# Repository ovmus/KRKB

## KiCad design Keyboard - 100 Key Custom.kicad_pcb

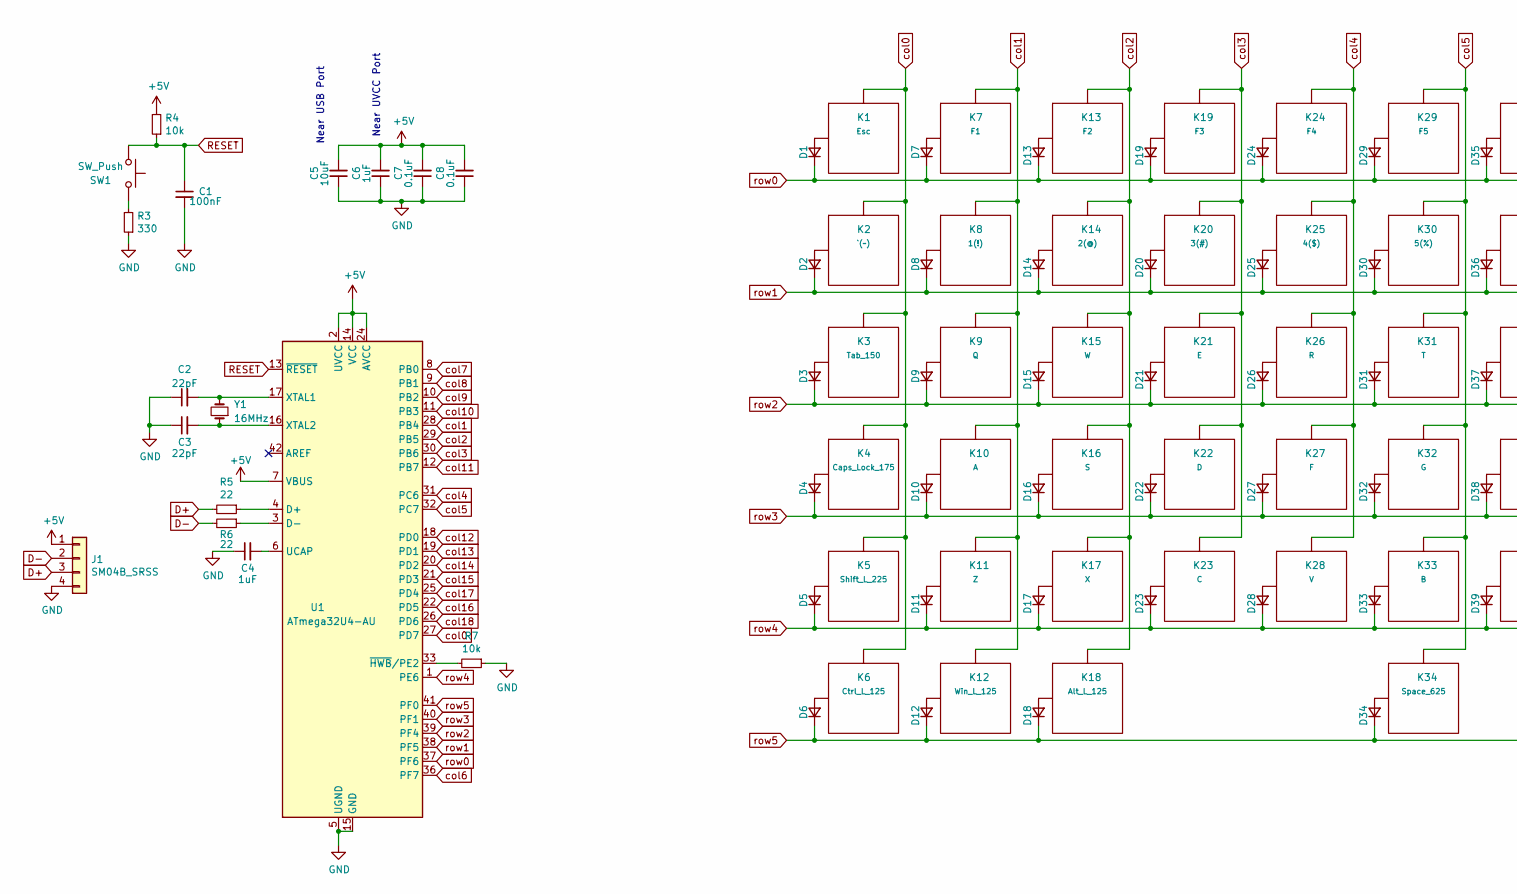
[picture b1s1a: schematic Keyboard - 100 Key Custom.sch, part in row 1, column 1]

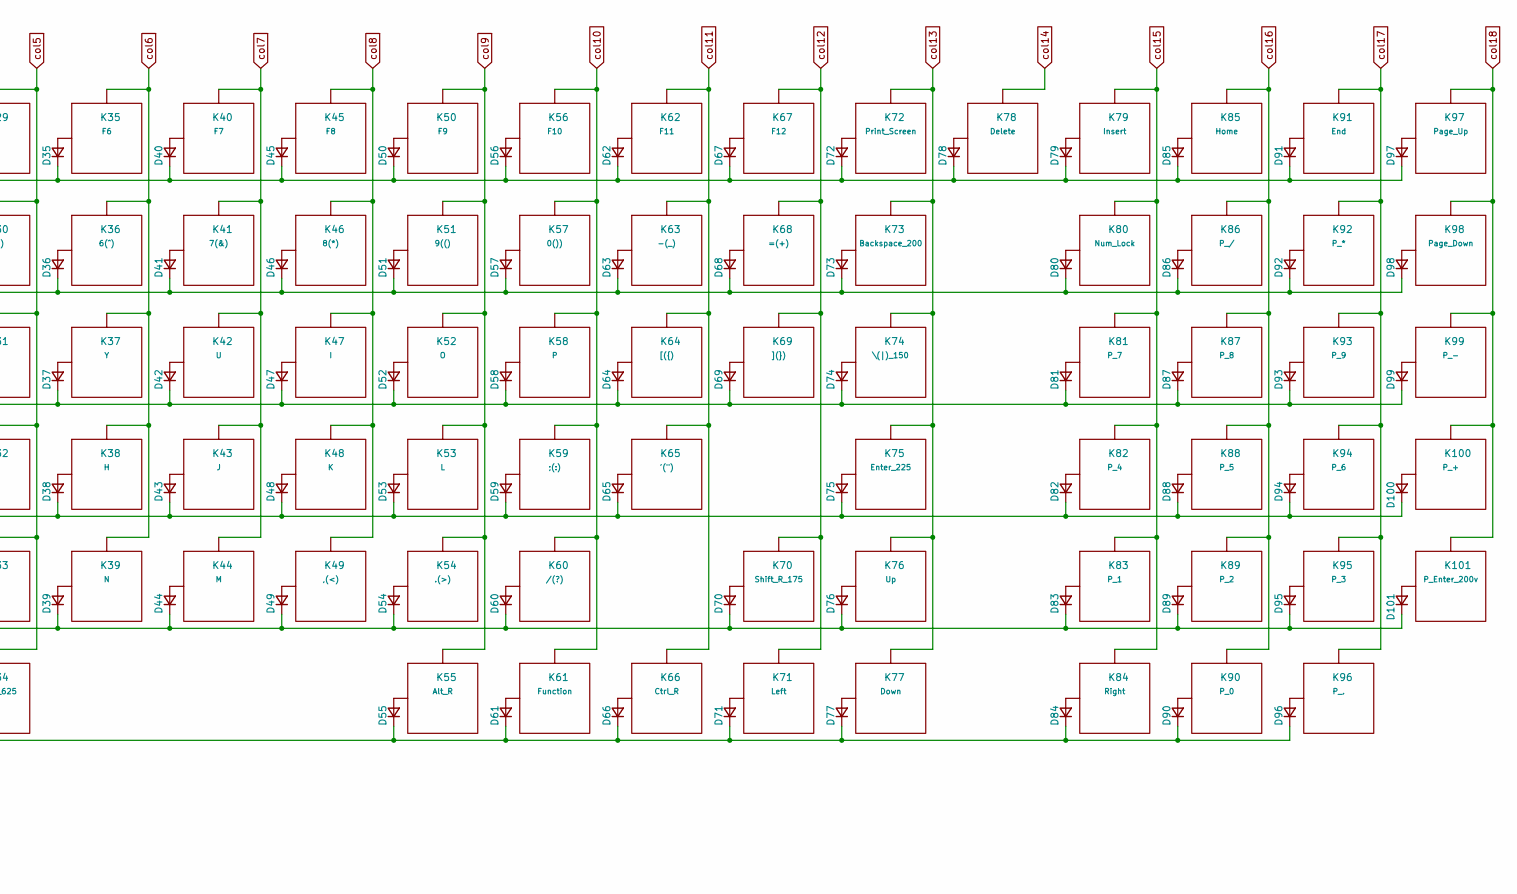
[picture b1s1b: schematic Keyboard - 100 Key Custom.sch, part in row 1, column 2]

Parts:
C1: 100nF; C_0805_2012Metric_Pad1.15x1.40mm_HandSolder
C2, C3: 22pF; C_0805_2012Metric_Pad1.15x1.40mm_HandSolder
C4, C6: 1uF; C_0805_2012Metric_Pad1.15x1.40mm_HandSolder
C5: 10uF; C_0805_2012Metric_Pad1.15x1.40mm_HandSolder
C7, C8: 0.1uF; C_0805_2012Metric_Pad1.15x1.40mm_HandSolder
D1, D2, D3, D4, D5, D6, D7, D8, D9, D10, D11, D12, D13, D14, D15, D16, D17, D18, D19, D20, D21, D22, D23, D24, D25, D26, D27, D28, D29, D30, D31, D32, D33, D34, D35, D36, D37, D38, D39, D40, D41, D42, D43, D44, D45, D46, D47, D48, D49, D50, D51, D52, D53, D54, D55, D56, D57, D58, D59, D60, D61, D62, D63, D64, D65, D66, D67, D68, D69, D70, D71, D72, D73, D74, D75, D76, D77, D78, D79, D80, D81, D82, D83, D84, D85, D86, D87, D88, D89, D90, D91, D92, D93, D94, D95, D96, D97, D98, D99, D100, D101: D_Small; D_SOD-123
J1: SM04B_SRSS; SM04B-SRSS
K1: Esc; MX100
K2: `(~~); MX100
K3: Tab_150; MX150
K4: Caps_Lock_175; MX175
K5: Shift_L_225; MX225
K6: Ctrl_L_125; MX125
K7: F1; MX100
K8: 1(!); MX100
K9: Q; MX100
K10: A; MX100
K11: Z; MX100
K12: Win_L_125; MX125
K13: F2; MX100
K14: 2(@); MX100
K15: W; MX100
K16: S; MX100
K17: X; MX100
K18: Alt_L_125; MX125
K19: F3; MX100
K20: 3(#); MX100
K21: E; MX100
K22: D; MX100
K23: C; MX100
K24: F4; MX100
K25: 4($); MX100
K26: R; MX100
K27: F; MX100
K28: V; MX100
K29: F5; MX100
K30: 5(%); MX100
K31: T; MX100
K32: G; MX100
K33: B; MX100
K34: Space_625; MX625R
K35: F6; MX100
K36: 6(^); MX100
K37: Y; MX100
K38: H; MX100
K39: N; MX100
K40: F7; MX100
K41: 7(&); MX100
K42: U; MX100
K43: J; MX100
K44: M; MX100
K45: F8; MX100
K46: 8(*); MX100
K47: I; MX100
K48: K; MX100
K49: ,(<); MX100
K50: F9; MX100
K51: 9((); MX100
K52: O; MX100
K53: L; MX100
K54: .(>); MX100
K55: Alt_R; MX100
K56: F10; MX100
K57: 0()); MX100
K58: P; MX100
K59: ;(:); MX100
K60: /(?); MX100
K61: Function; MX100
K62: F11; MX100
K63: -(_); MX100
K64: [({); MX100
K65: '(\"); MX100
K66: Ctrl_R; MX100
K67: F12; MX100
K68: =(+); MX100
K69: ](}); MX100
K70: Shift_R_175; MX175
K71: Left; MX100
K72: Print_Screen; MX100
K73: Backspace_200; MX200
K74: \\(|)_150; MX150
K75: Enter_225; MX225
K76: Up; MX100
K77: Down; MX100
K78: Delete; MX100
K79: Insert; MX100
K80: Num_Lock; MX100
K81: P_7; MX100
K82: P_4; MX100
K83: P_1; MX100
K84: Right; MX100
K85: Home; MX100
K86: P_/; MX100
K87: P_8; MX100
K88: P_5; MX100
K89: P_2; MX100
K90: P_0; MX100
K91: End; MX100
K92: P_*; MX100
K93: P_9; MX100
K94: P_6; MX100
K95: P_3; MX100
K96: P_.; MX100
K97: Page_Up; MX100
K98: Page_Down; MX100
K99: P_-; MX100
K100: P_+; MX100
K101: P_Enter_200v; MX200V
R3: 330; C_1206_3216Metric_Pad1.42x1.75mm_HandSolder
R4, R7: 10k; C_1206_3216Metric_Pad1.42x1.75mm_HandSolder
R5, R6: 22; C_1206_3216Metric_Pad1.42x1.75mm_HandSolder
SW1: SW_Push; K2-1187SQ-A4SW-06
U1: ATmega32U4-AU; TQPF-44_10x10mm_P0.8mm
Y1: 16MHz; Crystal_SMD_5032-2Pin_5.0x3.2mm_HandSoldering

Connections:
+5V: C5.2, C6.2, C7.2, C8.2, J1.1, R4.2, U1.2 (UVCC), U1.7 (VBUS), U1.14 (VCC), U1.24 (AVCC), U1.34 (VCC), U1.44 (AVCC)
D+: J1.3, R5.2
D-: J1.2, R6.2
GND: C1.2, C2.1, C3.1, C4.1, C5.1, C6.1, C7.1, C8.1, J1.4, R3.1, R7.1, U1.5 (UGND), U1.15 (GND), U1.23 (GND), U1.35 (GND), U1.43 (GND)
unnamed: C2.2, U1.17 (XTAL1), Y1.2
unnamed: C3.2, U1.16 (XTAL2), Y1.1
unnamed: C4.2, U1.6 (UCAP)
unnamed: D1.2 (A), K1.1 (Col)
unnamed: D2.2 (A), K2.1 (Col)
unnamed: D3.2 (A), K3.1 (Col)
unnamed: D4.2 (A), K4.1 (Col)
unnamed: D5.2 (A), K5.1 (Col)
unnamed: D6.2 (A), K6.1 (Col)
unnamed: D7.2 (A), K7.1 (Col)
unnamed: D8.2 (A), K8.1 (Col)
unnamed: D9.2 (A), K9.1 (Col)
unnamed: D10.2 (A), K10.1 (Col)
unnamed: D11.2 (A), K11.1 (Col)
unnamed: D12.2 (A), K12.1 (Col)
unnamed: D13.2 (A), K13.1 (Col)
unnamed: D14.2 (A), K14.1 (Col)
unnamed: D15.2 (A), K15.1 (Col)
unnamed: D16.2 (A), K16.1 (Col)
unnamed: D17.2 (A), K17.1 (Col)
unnamed: D18.2 (A), K18.1 (Col)
unnamed: D19.2 (A), K19.1 (Col)
unnamed: D20.2 (A), K20.1 (Col)
unnamed: D21.2 (A), K21.1 (Col)
unnamed: D22.2 (A), K22.1 (Col)
unnamed: D23.2 (A), K23.1 (Col)
unnamed: D24.2 (A), K24.1 (Col)
unnamed: D25.2 (A), K25.1 (Col)
unnamed: D26.2 (A), K26.1 (Col)
unnamed: D27.2 (A), K27.1 (Col)
unnamed: D28.2 (A), K28.1 (Col)
unnamed: D29.2 (A), K29.1 (Col)
unnamed: D30.2 (A), K30.1 (Col)
unnamed: D31.2 (A), K31.1 (Col)
unnamed: D32.2 (A), K32.1 (Col)
unnamed: D33.2 (A), K33.1 (Col)
unnamed: D34.2 (A), K34.1 (Col)
unnamed: D35.2 (A), K35.1 (Col)
unnamed: D36.2 (A), K36.1 (Col)
unnamed: D37.2 (A), K37.1 (Col)
unnamed: D38.2 (A), K38.1 (Col)
unnamed: D39.2 (A), K39.1 (Col)
unnamed: D40.2 (A), K40.1 (Col)
unnamed: D41.2 (A), K41.1 (Col)
unnamed: D42.2 (A), K42.1 (Col)
unnamed: D43.2 (A), K43.1 (Col)
unnamed: D44.2 (A), K44.1 (Col)
unnamed: D45.2 (A), K45.1 (Col)
unnamed: D46.2 (A), K46.1 (Col)
unnamed: D47.2 (A), K47.1 (Col)
unnamed: D48.2 (A), K48.1 (Col)
unnamed: D49.2 (A), K49.1 (Col)
unnamed: D50.2 (A), K50.1 (Col)
unnamed: D51.2 (A), K51.1 (Col)
unnamed: D52.2 (A), K52.1 (Col)
unnamed: D53.2 (A), K53.1 (Col)
unnamed: D54.2 (A), K54.1 (Col)
unnamed: D55.2 (A), K55.1 (Col)
unnamed: D56.2 (A), K56.1 (Col)
unnamed: D57.2 (A), K57.1 (Col)
unnamed: D58.2 (A), K58.1 (Col)
unnamed: D59.2 (A), K59.1 (Col)
unnamed: D60.2 (A), K60.1 (Col)
unnamed: D61.2 (A), K61.1 (Col)
unnamed: D62.2 (A), K62.1 (Col)
unnamed: D63.2 (A), K63.1 (Col)
unnamed: D64.2 (A), K64.1 (Col)
unnamed: D65.2 (A), K65.1 (Col)
unnamed: D66.2 (A), K66.1 (Col)
unnamed: D67.2 (A), K67.1 (Col)
unnamed: D68.2 (A), K68.1 (Col)
unnamed: D69.2 (A), K69.1 (Col)
unnamed: D70.2 (A), K70.1 (Col)
unnamed: D71.2 (A), K71.1 (Col)
unnamed: D72.2 (A), K72.1 (Col)
unnamed: D73.2 (A), K73.1 (Col)
unnamed: D74.2 (A), K74.1 (Col)
unnamed: D75.2 (A), K75.1 (Col)
unnamed: D76.2 (A), K76.1 (Col)
unnamed: D77.2 (A), K77.1 (Col)
unnamed: D78.2 (A), K78.1 (Col)
unnamed: D79.2 (A), K79.1 (Col)
unnamed: D80.2 (A), K80.1 (Col)
unnamed: D81.2 (A), K81.1 (Col)
unnamed: D82.2 (A), K82.1 (Col)
unnamed: D83.2 (A), K83.1 (Col)
unnamed: D84.2 (A), K84.1 (Col)
unnamed: D85.2 (A), K85.1 (Col)
unnamed: D86.2 (A), K86.1 (Col)
unnamed: D87.2 (A), K87.1 (Col)
unnamed: D88.2 (A), K88.1 (Col)
unnamed: D89.2 (A), K89.1 (Col)
unnamed: D90.2 (A), K90.1 (Col)
unnamed: D91.2 (A), K91.1 (Col)
unnamed: D92.2 (A), K92.1 (Col)
unnamed: D93.2 (A), K93.1 (Col)
unnamed: D94.2 (A), K94.1 (Col)
unnamed: D95.2 (A), K95.1 (Col)
unnamed: D96.2 (A), K96.1 (Col)
unnamed: D97.2 (A), K97.1 (Col)
unnamed: D98.2 (A), K98.1 (Col)
unnamed: D99.2 (A), K99.1 (Col)
unnamed: D100.2 (A), K100.1 (Col)
unnamed: D101.2 (A), K101.1 (Col)
unnamed: R3.2, SW1.2
unnamed: R5.1, U1.4 (D+)
unnamed: R6.1, U1.3 (D-)
unnamed: R7.2, U1.33 (~HWB~/PE2)
RESET: C1.1, R4.1, SW1.1, U1.13 (~RESET)
col0: K1.2 (Row), K2.2 (Row), K3.2 (Row), K4.2 (Row), K5.2 (Row), K6.2 (Row), U1.27 (PD7)
col1: K7.2 (Row), K8.2 (Row), K9.2 (Row), K10.2 (Row), K11.2 (Row), K12.2 (Row), U1.28 (PB4)
col2: K13.2 (Row), K14.2 (Row), K15.2 (Row), K16.2 (Row), K17.2 (Row), K18.2 (Row), U1.29 (PB5)
col3: K19.2 (Row), K20.2 (Row), K21.2 (Row), K22.2 (Row), K23.2 (Row), U1.30 (PB6)
col4: K24.2 (Row), K25.2 (Row), K26.2 (Row), K27.2 (Row), K28.2 (Row), U1.31 (PC6)
col5: K29.2 (Row), K30.2 (Row), K31.2 (Row), K32.2 (Row), K33.2 (Row), K34.2 (Row), U1.32 (PC7)
col6: K35.2 (Row), K36.2 (Row), K37.2 (Row), K38.2 (Row), K39.2 (Row), U1.36 (PF7)
col7: K40.2 (Row), K41.2 (Row), K42.2 (Row), K43.2 (Row), K44.2 (Row), U1.8 (PB0)
col8: K45.2 (Row), K46.2 (Row), K47.2 (Row), K48.2 (Row), K49.2 (Row), U1.9 (PB1)
col9: K50.2 (Row), K51.2 (Row), K52.2 (Row), K53.2 (Row), K54.2 (Row), K55.2 (Row), U1.10 (PB2)
col10: K56.2 (Row), K57.2 (Row), K58.2 (Row), K59.2 (Row), K60.2 (Row), K61.2 (Row), U1.11 (PB3)
col11: K62.2 (Row), K63.2 (Row), K64.2 (Row), K65.2 (Row), K66.2 (Row), U1.12 (PB7)
col12: K67.2 (Row), K68.2 (Row), K69.2 (Row), K70.2 (Row), K71.2 (Row), U1.18 (PD0)
col13: K72.2 (Row), K73.2 (Row), K74.2 (Row), K75.2 (Row), K76.2 (Row), K77.2 (Row), U1.19 (PD1)
col14: K78.2 (Row), U1.20 (PD2)
col15: K79.2 (Row), K80.2 (Row), K81.2 (Row), K82.2 (Row), K83.2 (Row), K84.2 (Row), U1.21 (PD3)
col16: K85.2 (Row), K86.2 (Row), K87.2 (Row), K88.2 (Row), K89.2 (Row), K90.2 (Row), U1.22 (PD5)
col17: K91.2 (Row), K92.2 (Row), K93.2 (Row), K94.2 (Row), K95.2 (Row), K96.2 (Row), U1.25 (PD4)
col18: K97.2 (Row), K98.2 (Row), K99.2 (Row), K100.2 (Row), K101.2 (Row), U1.26 (PD6)
row0: D1.1 (K), D7.1 (K), D13.1 (K), D19.1 (K), D24.1 (K), D29.1 (K), D35.1 (K), D40.1 (K), D45.1 (K), D50.1 (K), D56.1 (K), D62.1 (K), D67.1 (K), D72.1 (K), D78.1 (K), D79.1 (K), D85.1 (K), D91.1 (K), D97.1 (K), U1.37 (PF6)
row1: D2.1 (K), D8.1 (K), D14.1 (K), D20.1 (K), D25.1 (K), D30.1 (K), D36.1 (K), D41.1 (K), D46.1 (K), D51.1 (K), D57.1 (K), D63.1 (K), D68.1 (K), D73.1 (K), D80.1 (K), D86.1 (K), D92.1 (K), D98.1 (K), U1.38 (PF5)
row2: D3.1 (K), D9.1 (K), D15.1 (K), D21.1 (K), D26.1 (K), D31.1 (K), D37.1 (K), D42.1 (K), D47.1 (K), D52.1 (K), D58.1 (K), D64.1 (K), D69.1 (K), D74.1 (K), D81.1 (K), D87.1 (K), D93.1 (K), D99.1 (K), U1.39 (PF4)
row3: D4.1 (K), D10.1 (K), D16.1 (K), D22.1 (K), D27.1 (K), D32.1 (K), D38.1 (K), D43.1 (K), D48.1 (K), D53.1 (K), D59.1 (K), D65.1 (K), D75.1 (K), D82.1 (K), D88.1 (K), D94.1 (K), D100.1 (K), U1.40 (PF1)
row4: D5.1 (K), D11.1 (K), D17.1 (K), D23.1 (K), D28.1 (K), D33.1 (K), D39.1 (K), D44.1 (K), D49.1 (K), D54.1 (K), D60.1 (K), D70.1 (K), D76.1 (K), D83.1 (K), D89.1 (K), D95.1 (K), D101.1 (K), U1.1 (PE6)
row5: D6.1 (K), D12.1 (K), D18.1 (K), D34.1 (K), D55.1 (K), D61.1 (K), D66.1 (K), D71.1 (K), D77.1 (K), D84.1 (K), D90.1 (K), D96.1 (K), U1.41 (PF0)

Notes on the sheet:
Near USB Port
Near UVCC Port

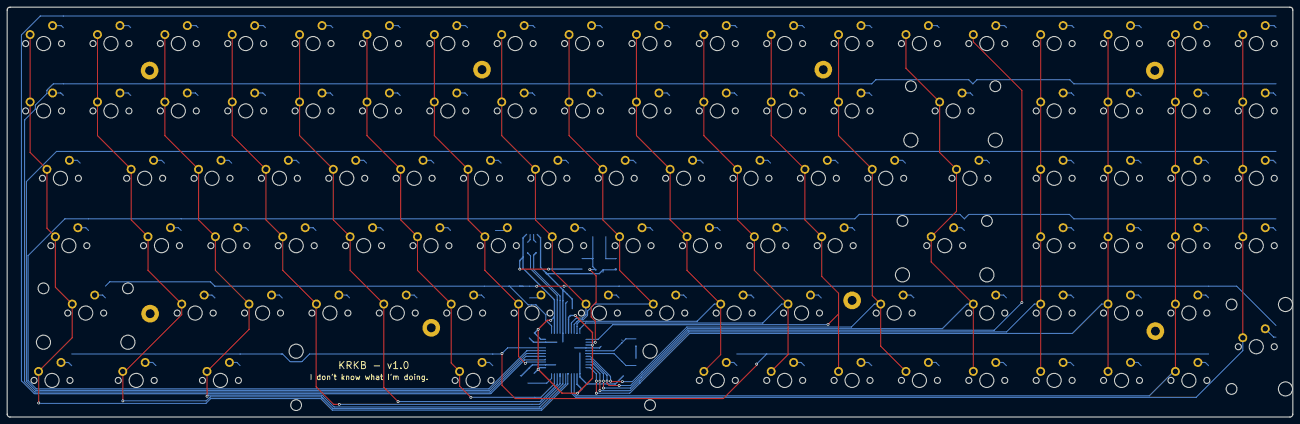
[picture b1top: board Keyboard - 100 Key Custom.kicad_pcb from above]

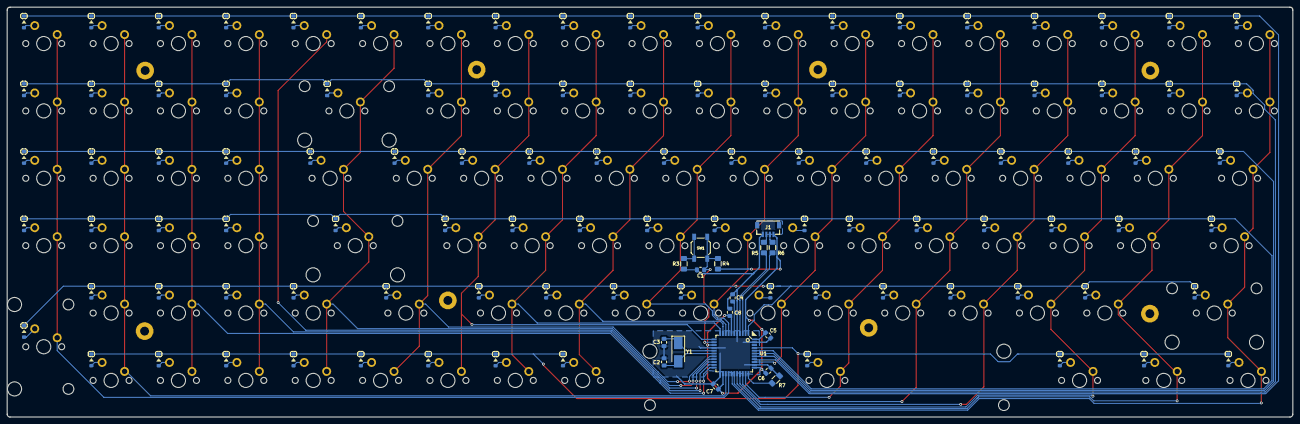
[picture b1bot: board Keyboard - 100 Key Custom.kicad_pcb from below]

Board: 2 copper layers, 363.5 x 115.9 mm, 227 parts (219 on the bottom side), 138 nets.

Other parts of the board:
HOLE: H**; MountingHole_2.5x5.0mm
HOLE#2, HOLE#3, HOLE#4, HOLE#5, HOLE#6, HOLE#7, HOLE#8: H**; MountingHole_2.5x5.0mm

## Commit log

2020-04-09 Added all files to this point.
2020-04-09 Update Keyboard - 100 Key Custom.kicad_pcb-bak
2020-04-12 Updated USB-C connector to interface with Daughterboard instead
2020-04-12 Started tracing
2020-04-13 Removed traces and changed MCU package & footprint
2020-04-14 Placed components roughly and traced rows and columns.
2020-04-21 Added traces besides rows/columns
2020-04-22 Replaced MCU with hand-solder model and retraced.
2020-05-04 Finished Running Traces
2020-05-05 Created Gerber Files
